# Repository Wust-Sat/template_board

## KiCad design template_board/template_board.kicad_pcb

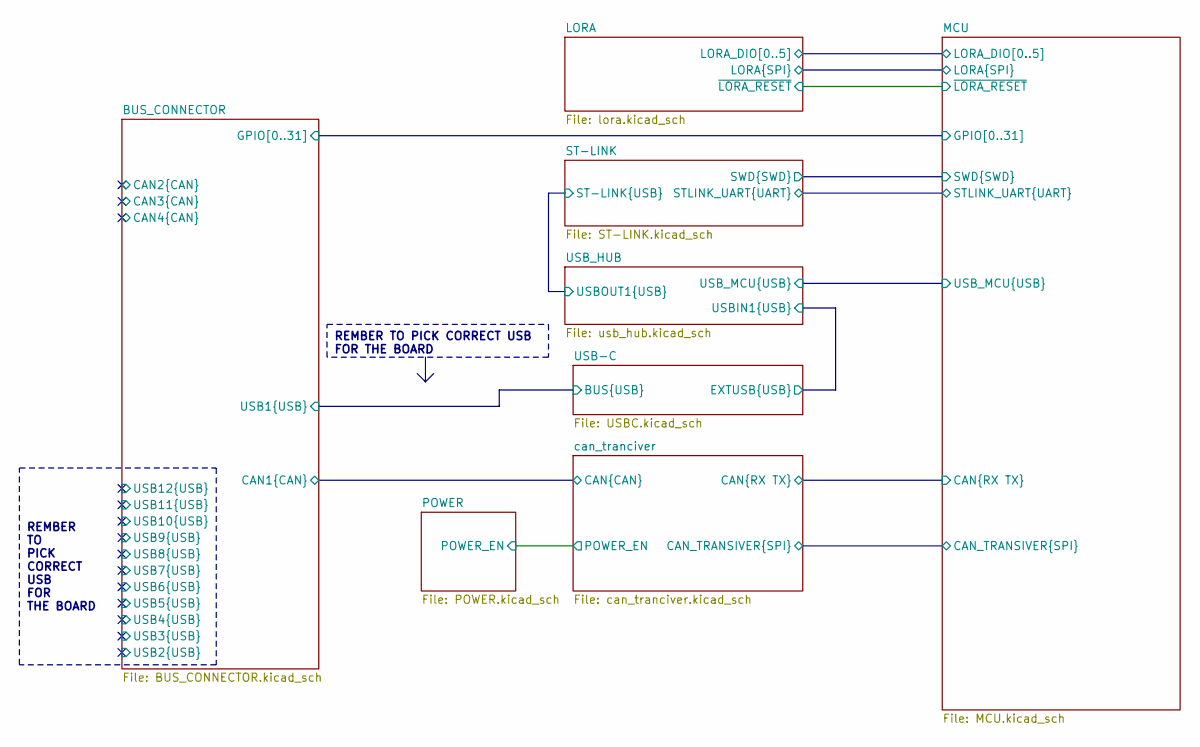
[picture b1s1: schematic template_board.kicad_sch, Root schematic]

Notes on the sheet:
REMBER TO PICK CORRECT USB FOR THE BOARD
REMBER TO PICK CORRECT USB FOR THE BOARD

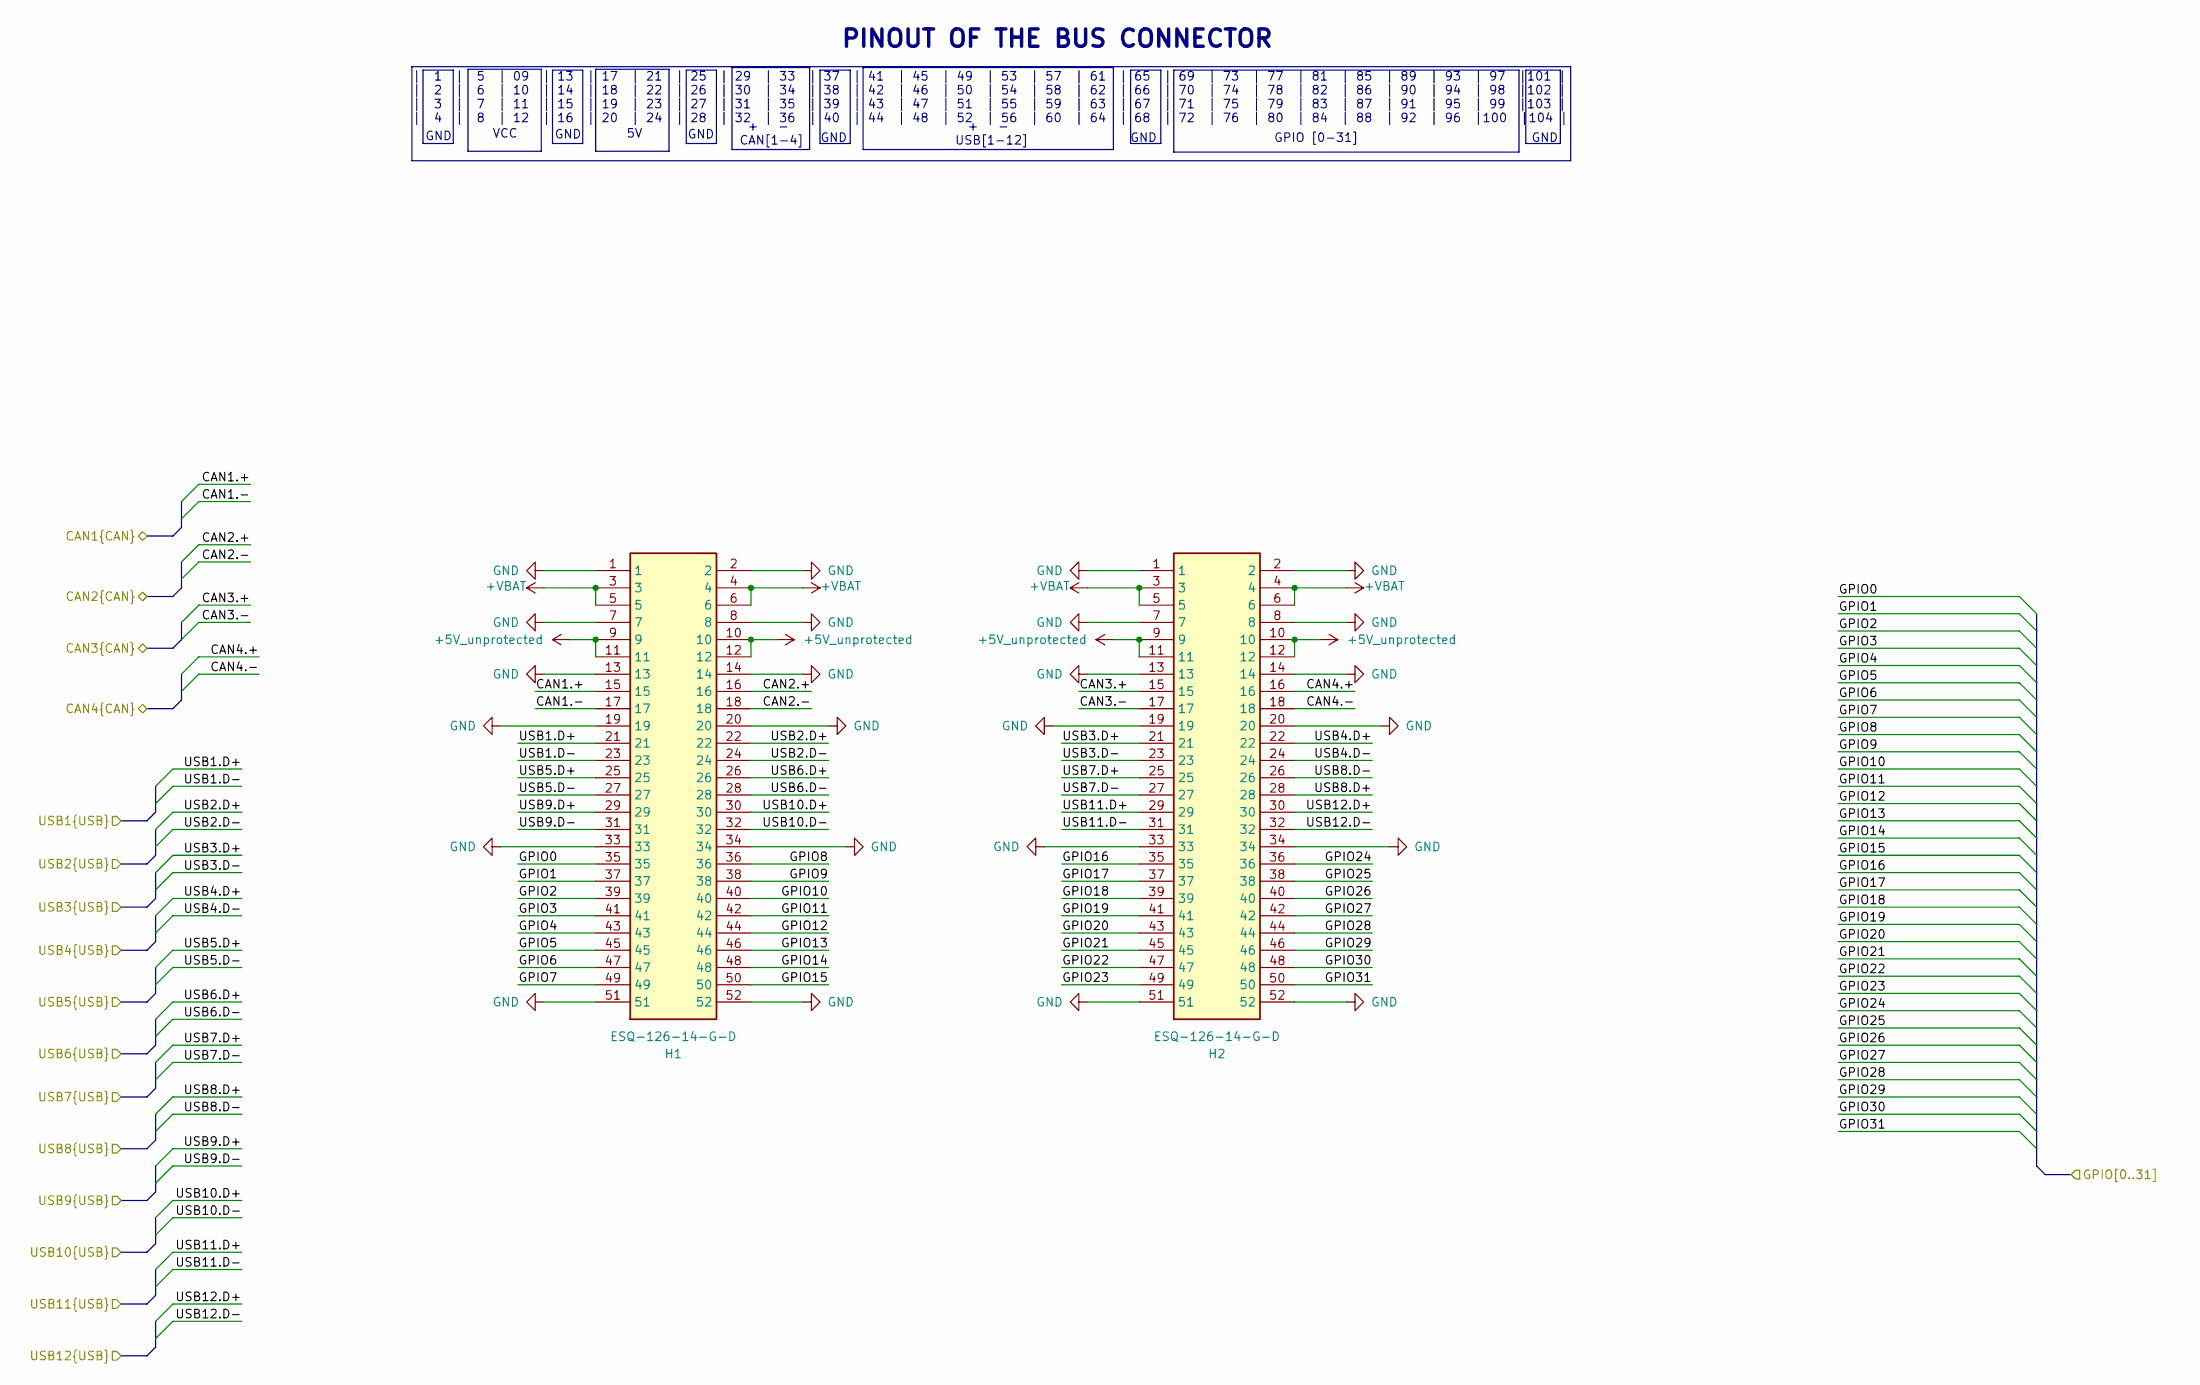
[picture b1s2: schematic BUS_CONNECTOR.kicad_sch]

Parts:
H1, H2: ESQ-126-14-G-D; ESQ-126-Y-X-D; Manufacturer_Part_Number ESQ-126-14-G-D; Mouser Part Number 200-ESQ12614GD

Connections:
+5V_unprotected: H1.9, H1.10, H1.11, H1.12, H2.9, H2.10, H2.11, H2.12; also elsewhere on the board
+VBAT: H1.3, H1.4, H1.5, H1.6, H2.3, H2.4, H2.5, H2.6
/BUS_CONNECTOR/CAN1.+: H1.15; also elsewhere on the board
/BUS_CONNECTOR/CAN1.-: H1.17; also elsewhere on the board
/BUS_CONNECTOR/CAN2.+: H1.16
/BUS_CONNECTOR/CAN2.-: H1.18
/BUS_CONNECTOR/CAN3.+: H2.15
/BUS_CONNECTOR/CAN3.-: H2.17
/BUS_CONNECTOR/CAN4.+: H2.16
/BUS_CONNECTOR/CAN4.-: H2.18
/BUS_CONNECTOR/GPIO0: H1.35; also elsewhere on the board
/BUS_CONNECTOR/GPIO1: H1.37; also elsewhere on the board
/BUS_CONNECTOR/GPIO2: H1.39; also elsewhere on the board
/BUS_CONNECTOR/GPIO3: H1.41; also elsewhere on the board
/BUS_CONNECTOR/GPIO4: H1.43; also elsewhere on the board
/BUS_CONNECTOR/GPIO5: H1.45
/BUS_CONNECTOR/GPIO6: H1.47
/BUS_CONNECTOR/GPIO7: H1.49
/BUS_CONNECTOR/GPIO8: H1.36; also elsewhere on the board
/BUS_CONNECTOR/GPIO9: H1.38; also elsewhere on the board
/BUS_CONNECTOR/GPIO10: H1.40; also elsewhere on the board
/BUS_CONNECTOR/GPIO11: H1.42; also elsewhere on the board
/BUS_CONNECTOR/GPIO12: H1.44; also elsewhere on the board
/BUS_CONNECTOR/GPIO13: H1.46
/BUS_CONNECTOR/GPIO14: H1.48
/BUS_CONNECTOR/GPIO15: H1.50
/BUS_CONNECTOR/GPIO16: H2.35; also elsewhere on the board
/BUS_CONNECTOR/GPIO17: H2.37; also elsewhere on the board
/BUS_CONNECTOR/GPIO18: H2.39; also elsewhere on the board
/BUS_CONNECTOR/GPIO19: H2.41; also elsewhere on the board
/BUS_CONNECTOR/GPIO20: H2.43
/BUS_CONNECTOR/GPIO21: H2.45
/BUS_CONNECTOR/GPIO22: H2.47
/BUS_CONNECTOR/GPIO23: H2.49
/BUS_CONNECTOR/GPIO24: H2.36; also elsewhere on the board
/BUS_CONNECTOR/GPIO25: H2.38; also elsewhere on the board
/BUS_CONNECTOR/GPIO26: H2.40; also elsewhere on the board
/BUS_CONNECTOR/GPIO27: H2.42; also elsewhere on the board
/BUS_CONNECTOR/GPIO28: H2.44
/BUS_CONNECTOR/GPIO29: H2.46
/BUS_CONNECTOR/GPIO30: H2.48
/BUS_CONNECTOR/GPIO31: H2.50
/BUS_CONNECTOR/USB1.D+: H1.21; also elsewhere on the board
/BUS_CONNECTOR/USB1.D-: H1.23; also elsewhere on the board
/BUS_CONNECTOR/USB2.D+: H1.22
/BUS_CONNECTOR/USB2.D-: H1.24
/BUS_CONNECTOR/USB3.D+: H2.21
/BUS_CONNECTOR/USB3.D-: H2.23
/BUS_CONNECTOR/USB4.D+: H2.22
/BUS_CONNECTOR/USB4.D-: H2.24
/BUS_CONNECTOR/USB5.D+: H1.25
/BUS_CONNECTOR/USB5.D-: H1.27
/BUS_CONNECTOR/USB6.D+: H1.26
/BUS_CONNECTOR/USB6.D-: H1.28
/BUS_CONNECTOR/USB7.D+: H2.25
/BUS_CONNECTOR/USB7.D-: H2.27
/BUS_CONNECTOR/USB8.D+: H2.28
/BUS_CONNECTOR/USB8.D-: H2.26
/BUS_CONNECTOR/USB9.D+: H1.29
/BUS_CONNECTOR/USB9.D-: H1.31
/BUS_CONNECTOR/USB10.D+: H1.30
/BUS_CONNECTOR/USB10.D-: H1.32
/BUS_CONNECTOR/USB11.D+: H2.29
/BUS_CONNECTOR/USB11.D-: H2.31
/BUS_CONNECTOR/USB12.D+: H2.30
/BUS_CONNECTOR/USB12.D-: H2.32
GND: H1.1, H1.2, H1.7, H1.8, H1.13, H1.14, H1.19, H1.20, H1.33, H1.34, H1.51, H1.52, H2.1, H2.2, H2.7, H2.8, H2.13, H2.14, H2.19, H2.20, H2.33, H2.34, H2.51, H2.52; also elsewhere on the board

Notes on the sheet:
+ - CAN[1-4]
PINOUT OF THE BUS CONNECTOR
GND
+ - USB[1-12]
VCC
| 1 | 5 | 09 | 13 | 17 | 21 | 25 | 29 | 33 | 37 | 41 | 45 | 49 | 53 | 57 | 61 | 65 | 69 | 73 | 77 | 81 | 85 | 89 | 93 | 97 |101 | | 2 | 6 | 10 | 14 | 18 | 22 | 26 | 30 | 34 | 38 | 42 | 46 | 50 | 54 | 58 | 62 | 66 | 70 | 74 | 78 | 82 | 86 | 90 | 94 | 98 |102 | | 3 | 7 | 11 | 15 | 19 | 23 | 27 | 31 |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
GPIO [0-31]

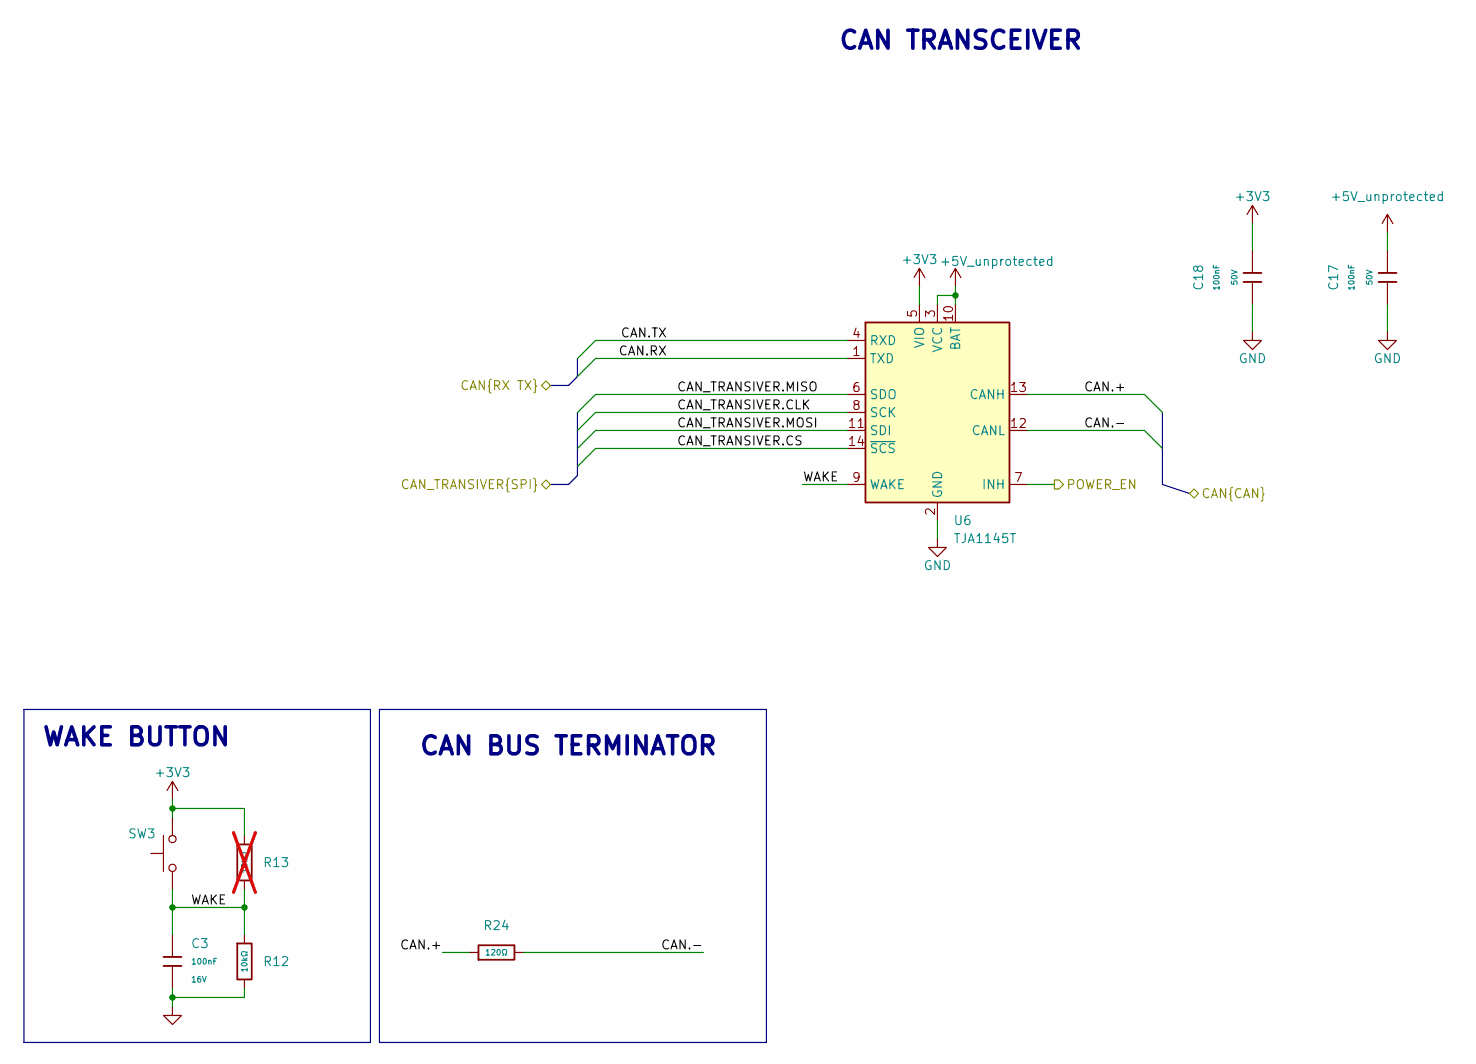
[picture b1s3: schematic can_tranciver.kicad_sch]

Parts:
C3: 100nF; C_0402; Voltage Rated 16V; Tolerance ±10%; Part CL05B104KO5NNNC; LCSC C1525
C17, C18: 100nF; C_0402; Voltage Rated 50V; Tolerance ±10%; Part CL05B104KB54PNC; LCSC C307331
R12: 10kΩ; R_0402; Overload Voltage (Max) 50V; Tolerance ±1%; Part 0402WGF1002TCE; LCSC C25744
R13: 10kΩ; R_0402; Overload Voltage (Max) 50V; Tolerance ±1%; Part 0402WGF1002TCE; LCSC C25744; not fitted
R24: 120Ω; R_0603; Overload Voltage (Max) 75V; Tolerance ±1%; Part 0603WAF1200T5E; LCSC C22787
SW3: SW_Push; TS1088R02026; LCSC C455280
U6: TJA1145T; SOIC-14_3.9x8.7mm_P1.27mm

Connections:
+3V3: C18.2, R13.1, SW3.2, U6.5 (VIO); also elsewhere on the board
+5V_unprotected: C17.2, U6.3 (VCC), U6.10 (BAT); also elsewhere on the board
/BUS_CONNECTOR/CAN1.+: R24.1, U6.13 (CANH); also elsewhere on the board
/BUS_CONNECTOR/CAN1.-: R24.2, U6.12 (CANL); also elsewhere on the board
/MCU/CAN.RX: U6.1 (TXD); also elsewhere on the board
/MCU/CAN.TX: U6.4 (RXD); also elsewhere on the board
/MCU/CAN_TRANSIVER.CLK: U6.8 (SCK); also elsewhere on the board
/MCU/CAN_TRANSIVER.CS: U6.14 (~SCS); also elsewhere on the board
/MCU/CAN_TRANSIVER.MISO: U6.6 (SDO); also elsewhere on the board
/MCU/CAN_TRANSIVER.MOSI: U6.11 (SDI); also elsewhere on the board
/POWER/POWER_EN: U6.7 (INH); also elsewhere on the board
/can_tranciver/WAKE: C3.1, R12.1, R13.2, SW3.1, U6.9 (WAKE)
GND: C3.2, C17.1, C18.1, R12.2, U6.2 (GND); also elsewhere on the board

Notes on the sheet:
CAN TRANSCEIVER
CAN BUS TERMINATOR
WAKE BUTTON

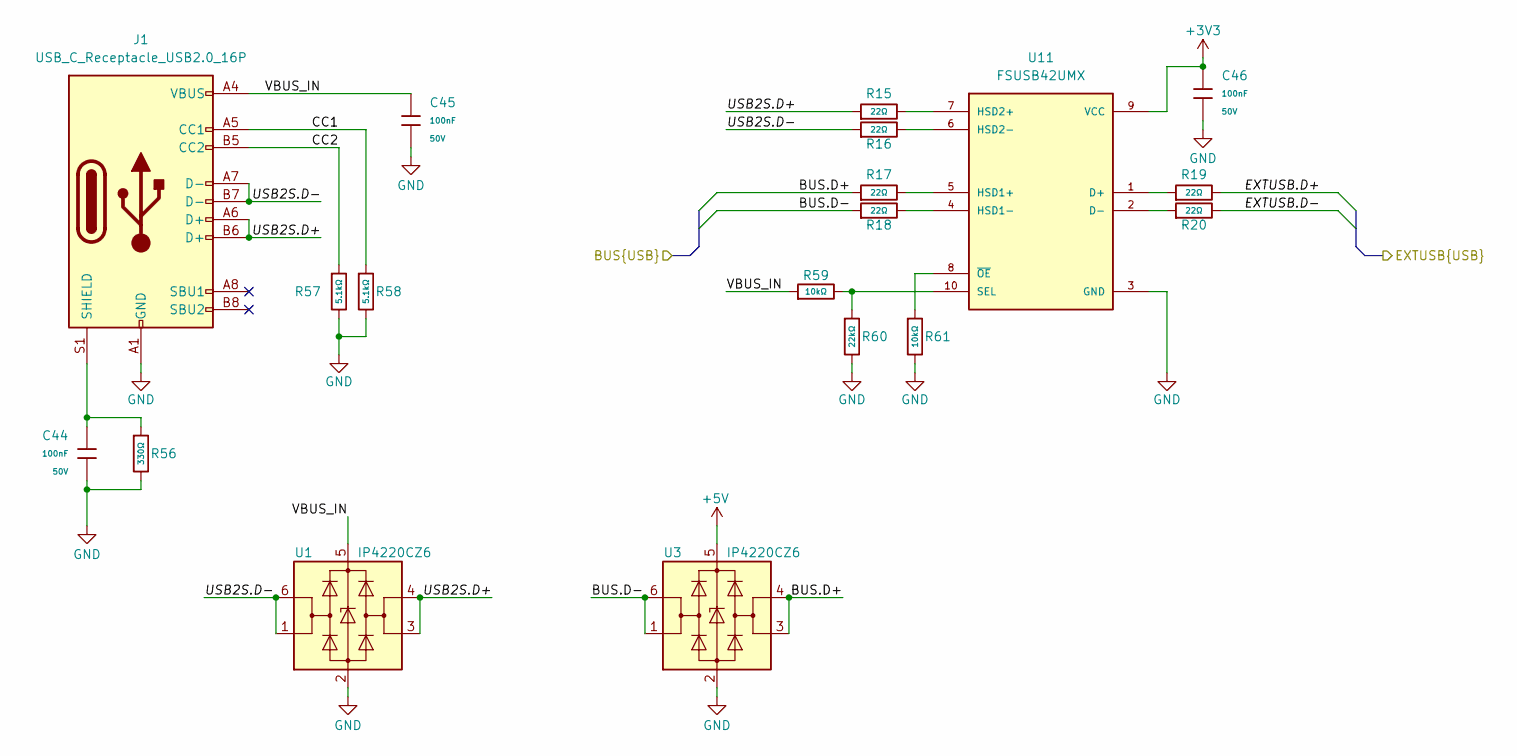
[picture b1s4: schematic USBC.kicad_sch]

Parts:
C44, C45, C46: 100nF; C_0402; Voltage Rated 50V; Tolerance ±10%; Part CL05B104KB54PNC; LCSC C307331
J1: USB_C_Receptacle_USB2.0_16P; USB_C_Receptacle_GCT_USB4105-xx-A_16P_TopMnt_Horizontal
R15, R16, R17, R18, R19, R20: 22Ω; R_0402; Overload Voltage (Max) 50V; Tolerance ±1%; Part 0402WGF220JTCE; LCSC C25092
R56: 330Ω; R_0402; Overload Voltage (Max) 50V; Tolerance ±1%; Part 0402WGF3300TCE; LCSC C25104
R57, R58: 5.1kΩ; R_0402; Overload Voltage (Max) 50V; Tolerance ±1%; Part 0402WGF5101TCE; LCSC C25905
R59, R61: 10kΩ; R_0402; Overload Voltage (Max) 50V; Tolerance ±1%; Part 0402WGF1002TCE; LCSC C25744
R60: 22kΩ; R_0402; Overload Voltage (Max) 50V; Tolerance ±1%; Part 0402WGF2202TCE; LCSC C25768
U1, U3: IP4220CZ6; SOT-23-6
U11: FSUSB42UMX; UQFN-10_1.4x1.8mm_P0.4mm; PARTREV 1.25

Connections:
+3V3: C46.1, U11.9 (VCC); also elsewhere on the board
+5V: U3.5 (VBUS); also elsewhere on the board
/BUS_CONNECTOR/USB1.D+: R17.1, U3.3 (I/O2), U3.4 (I/O2); also elsewhere on the board
/BUS_CONNECTOR/USB1.D-: R18.1, U3.1 (I/O1), U3.6 (I/O1); also elsewhere on the board
/USB-C/CC1: J1.A5 (CC1), R58.1
/USB-C/CC2: J1.B5 (CC2), R57.1
/USB-C/EXTUSB.D+: R19.2; also elsewhere on the board
/USB-C/EXTUSB.D-: R20.2; also elsewhere on the board
/USB-C/USB2S.D+: J1.A6 (D+), J1.B6 (D+), R15.1, U1.3 (I/O2), U1.4 (I/O2)
/USB-C/USB2S.D-: J1.A7 (D-), J1.B7 (D-), R16.1, U1.1 (I/O1), U1.6 (I/O1)
/USB-C/VBUS_IN: C45.1, J1.A4 (VBUS), J1.A9 (VBUS), J1.B4 (VBUS), J1.B9 (VBUS), R59.1, U1.5 (VBUS)
GND: C44.2, C45.2, C46.2, J1.A1 (GND), J1.A12 (GND), J1.B1 (GND), J1.B12 (GND), R56.2, R57.2, R58.2, R60.2, R61.2, U1.2 (GND), U3.2 (GND), U11.3 (GND); also elsewhere on the board
unnamed: C44.1, J1.S1 (SHIELD), R56.1
unnamed: R19.1, U11.1 (D+)
unnamed: R20.1, U11.2 (D-)
unnamed: R17.2, U11.5 (HSD1+)
unnamed: R18.2, U11.4 (HSD1-)
unnamed: R15.2, U11.7 (HSD2+)
unnamed: R16.2, U11.6 (HSD2-)
unnamed: R59.2, R60.1, U11.10 (SEL)
unnamed: R61.1, U11.8 (~OE)

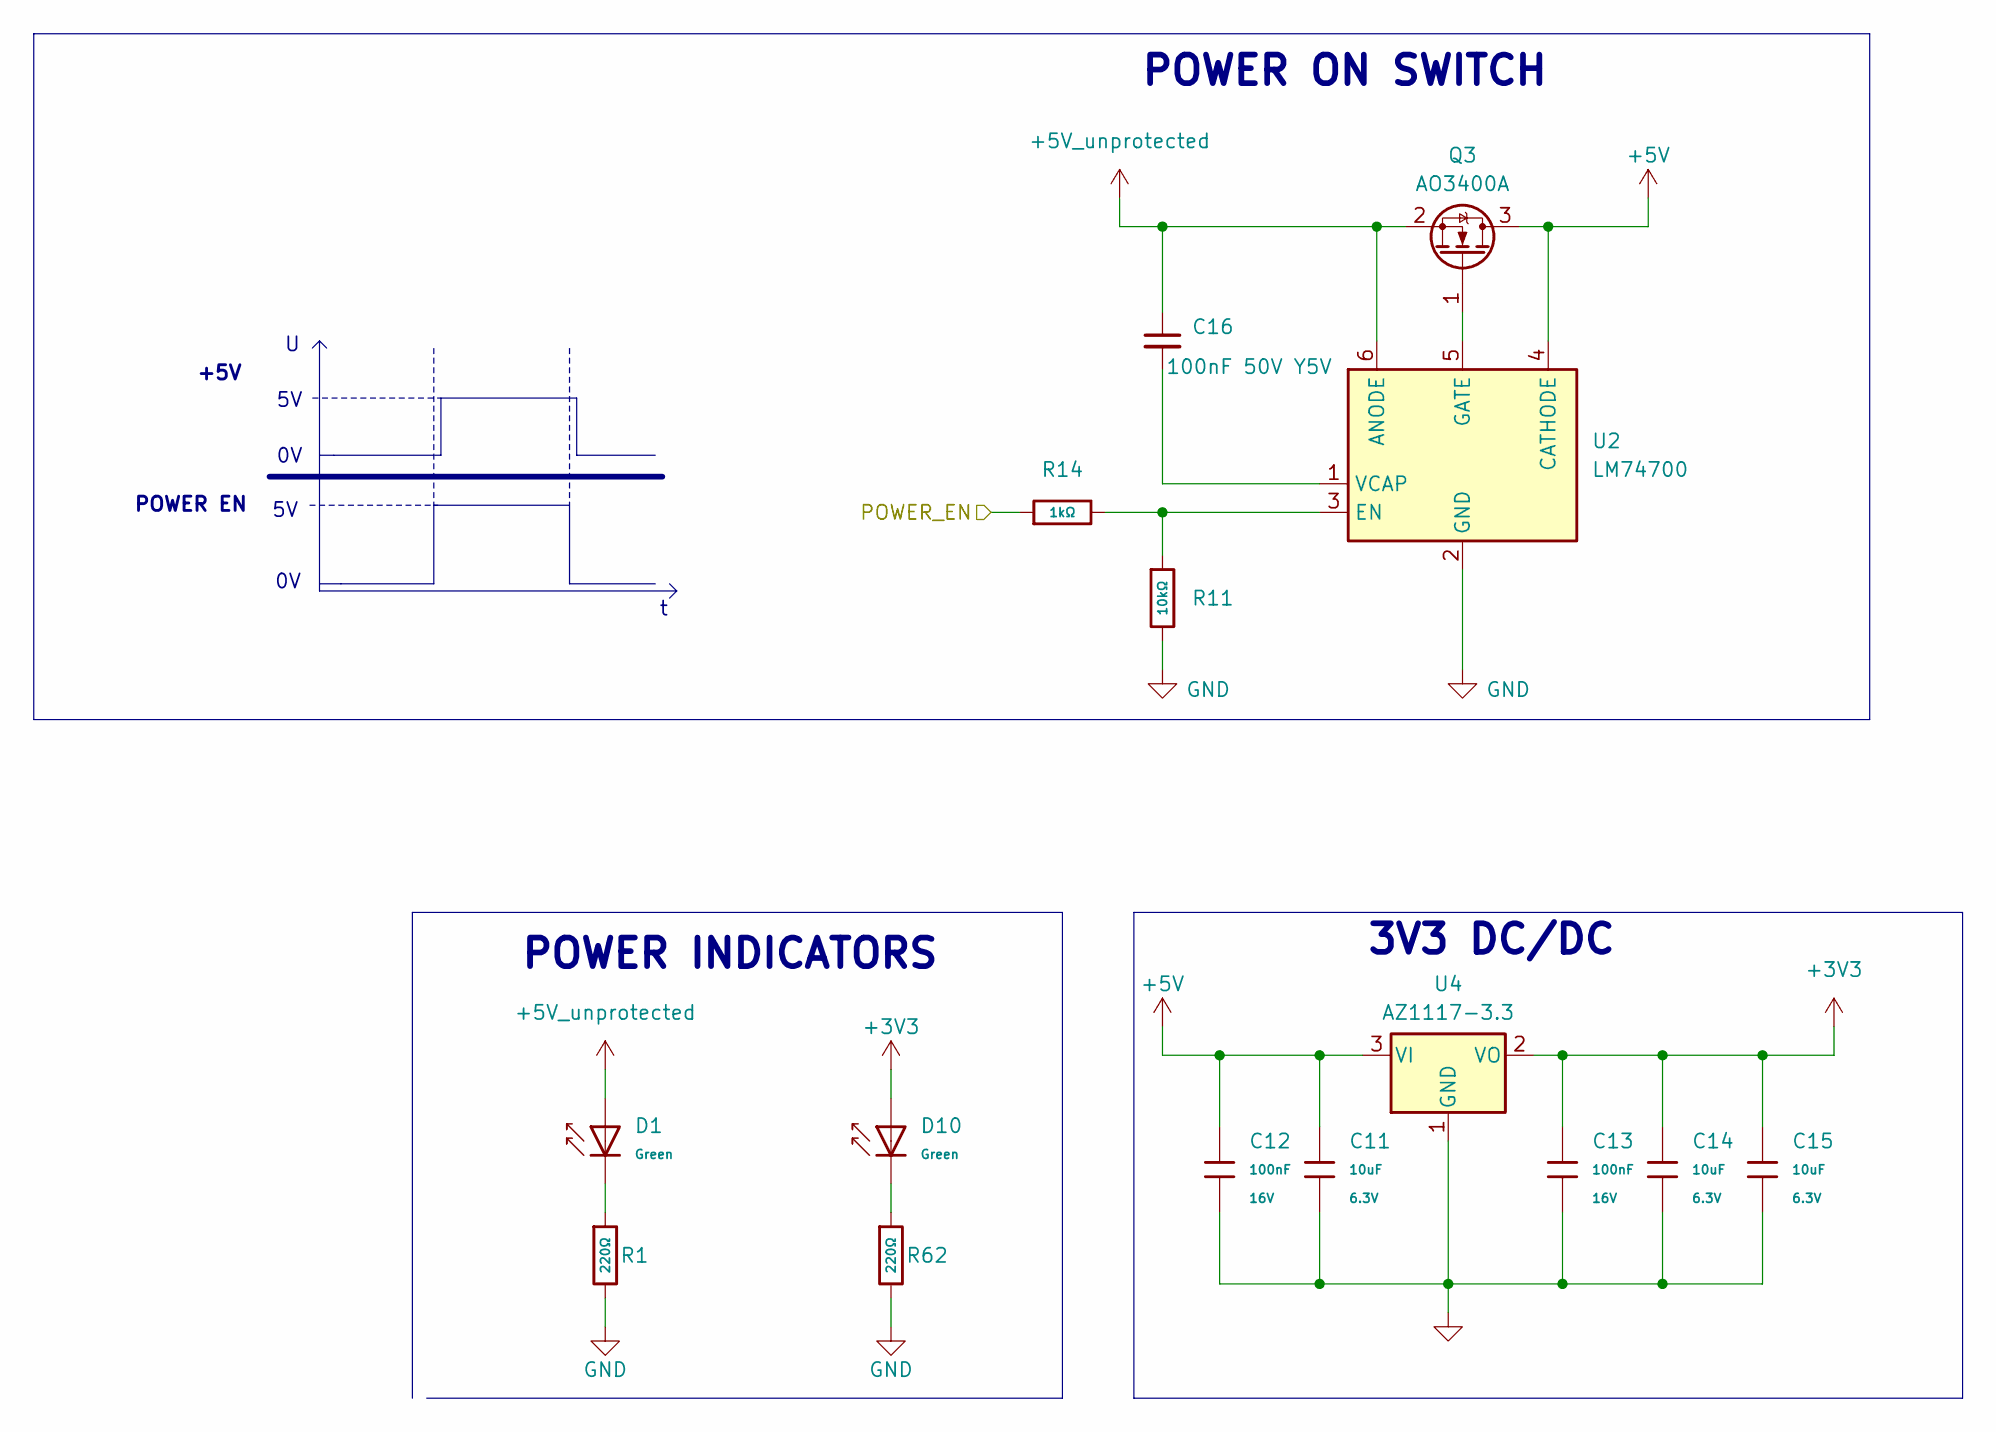
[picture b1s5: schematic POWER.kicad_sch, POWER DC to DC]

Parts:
C11, C14, C15: 10uF; C_0402; Voltage Rated 6.3V; Tolerance ±20%; Part CL05A106MQ5NUNC; LCSC C15525
C12, C13: 100nF; C_0402; Voltage Rated 16V; Tolerance ±10%; Part CL05B104KO5NNNC; LCSC C1525
C16: 100nF 50V Y5V; C_0402_1005Metric
D1, D10: Green; D_0603; Part 19-217/GHC-YR1S2/6T; LCSC C2986059
Q3: AO3400A; SOT-23
R1, R62: 220Ω; R_0402; Overload Voltage (Max) 50V; Tolerance ±1%; Part 0402WGF2200TCE; LCSC C25091
R11: 10kΩ; R_0402; Overload Voltage (Max) 50V; Tolerance ±1%; Part 0402WGF1002TCE; LCSC C25744
R14: 1kΩ; R_0402; Overload Voltage (Max) 50V; Tolerance ±1%; Part 0402WGF1001TCE; LCSC C11702
U2: LM74700; SOT-23-6
U4: AZ1117-3.3; SOT-223-3_TabPin2

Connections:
+3V3: C13.1, C14.1, C15.1, D10.2, U4.2 (VO); also elsewhere on the board
+5V: C11.1, C12.1, Q3.3 (D), U2.4 (CATHODE), U4.3 (VI); also elsewhere on the board
+5V_unprotected: C16.1, D1.2, Q3.2 (S), U2.6 (ANODE); also elsewhere on the board
/POWER/POWER_EN: R14.1; also elsewhere on the board
GND: C11.2, C12.2, C13.2, C14.2, C15.2, R1.2, R11.2, R62.2, U2.2 (GND), U4.1 (GND); also elsewhere on the board
unnamed: D1.1, R1.1
unnamed: D10.1, R62.1
unnamed: Q3.1 (G), U2.5 (GATE)
unnamed: R11.1, R14.2, U2.3 (EN)
unnamed: C16.2, U2.1 (VCAP)

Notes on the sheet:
3V3 DC/DC
POWER EN
+5V
POWER ON SWITCH
POWER INDICATORS

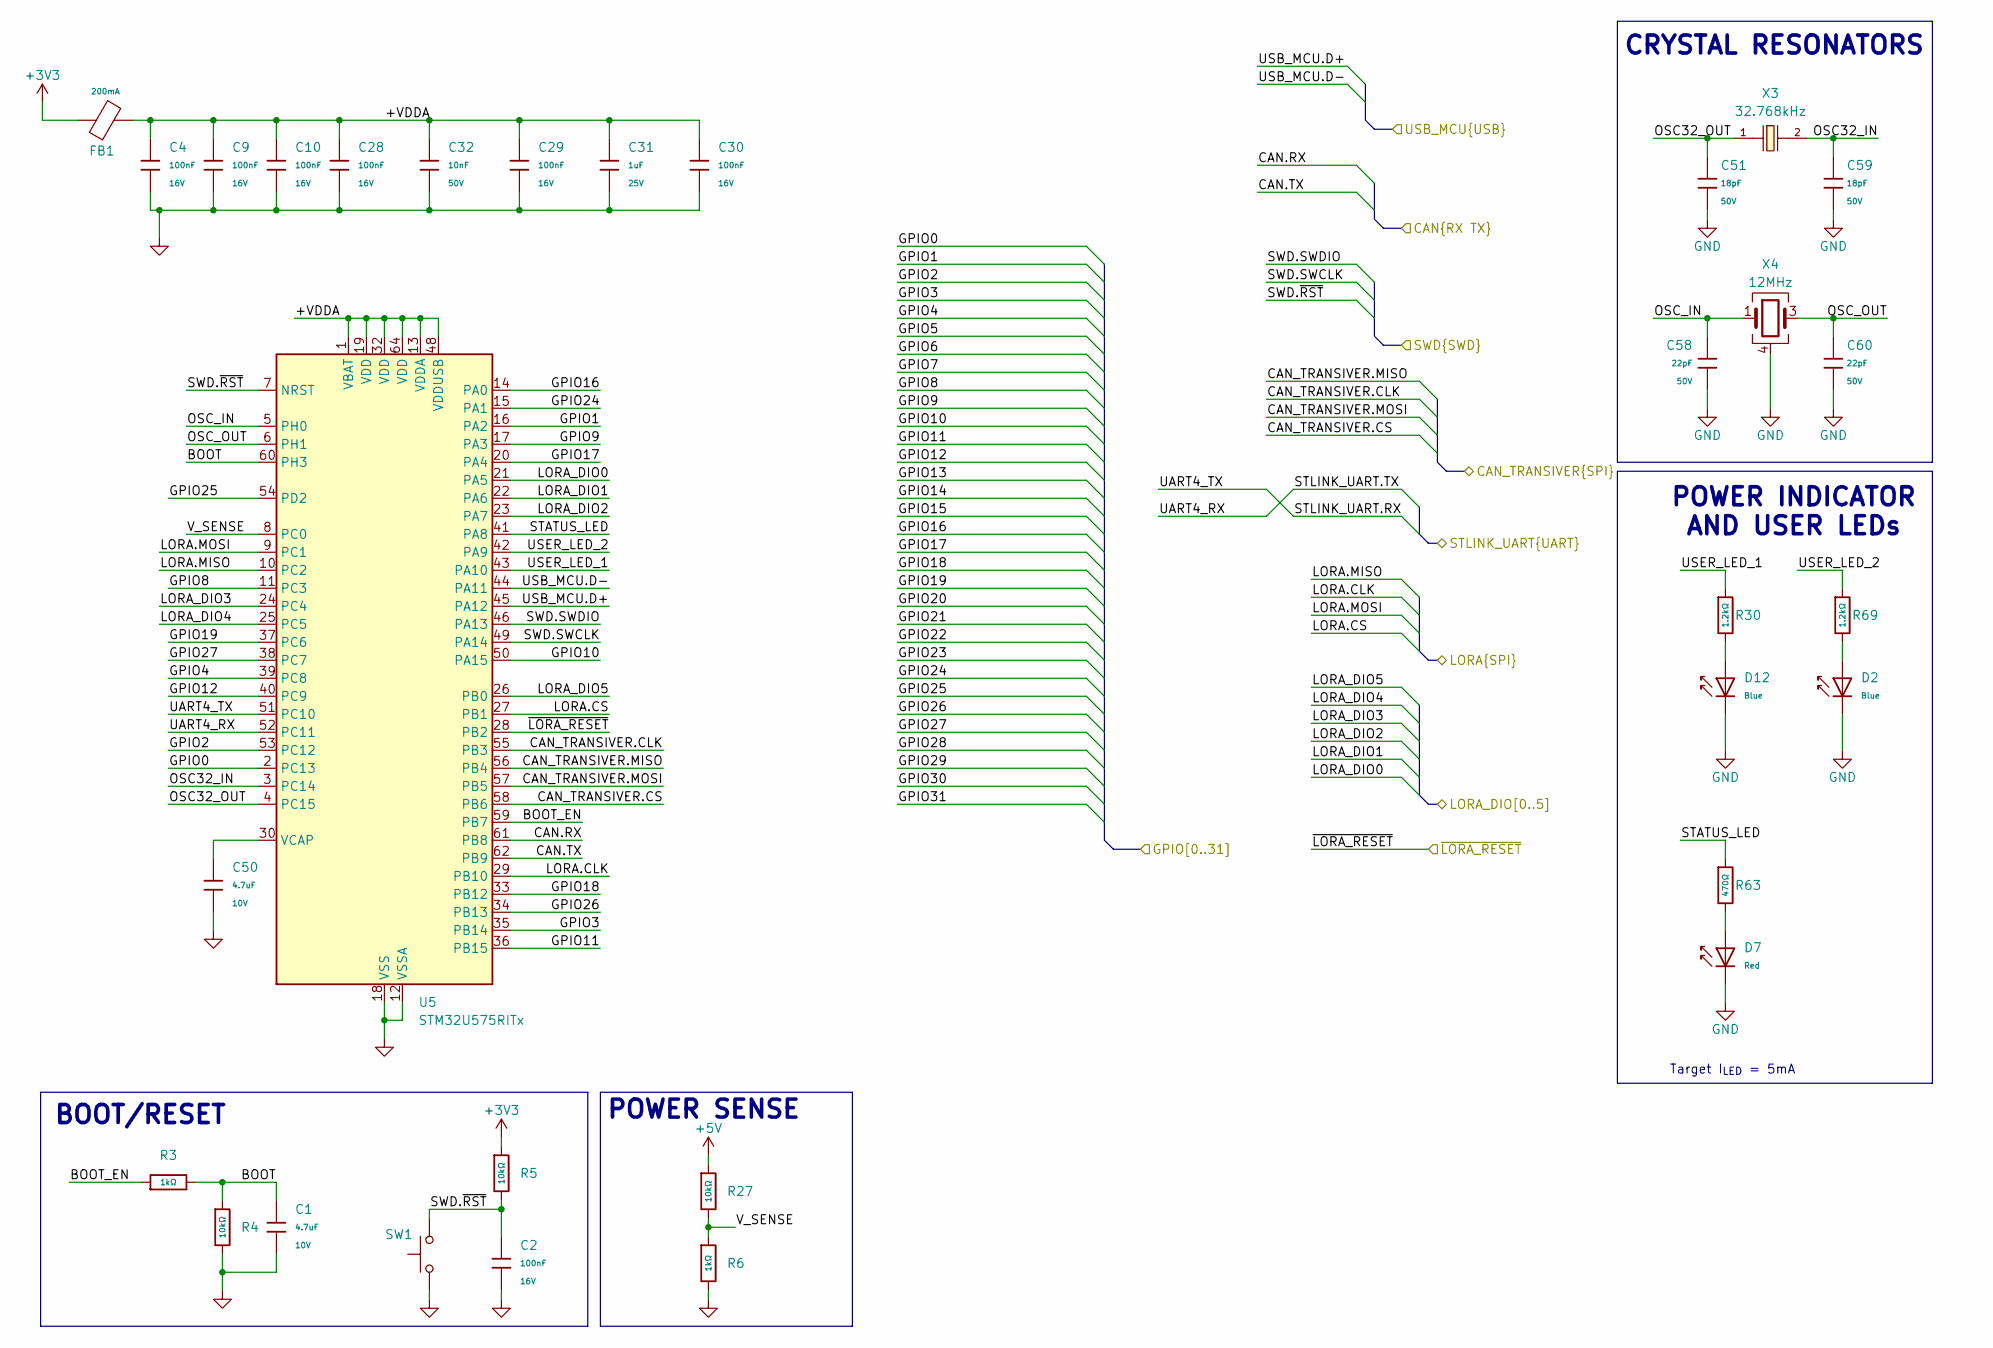
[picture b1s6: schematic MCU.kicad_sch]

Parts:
C1, C50: 4.7uF; C_0402; Voltage Rated 10V; Tolerance ±20%; Part CL05A475MP5NRNC; LCSC C23733
C2, C4, C9, C10, C28, C29, C30: 100nF; C_0402; Voltage Rated 16V; Tolerance ±10%; Part CL05B104KO5NNNC; LCSC C1525
C31: 1uF; C_0402; Voltage Rated 25V; Tolerance ±10%; Part CL05A105KA5NQNC; LCSC C52923
C32: 10nF; C_0402; Voltage Rated 50V; Tolerance ±10%; Part CL05B103KB5NNNC; LCSC C15195
C51, C59: 18pF; C_0402; Voltage Rated 50V; Tolerance ±5%; Part 0402CG180J500NT; LCSC C1549
C58, C60: 22pF; C_0402; Voltage Rated 50V; Tolerance ±5%; Part 0402CG220J500NT; LCSC C1555
D2, D12: Blue; D_0603; Part 19-217/BHC-ZL1M2RY/6T; LCSC C2986058
D7: Red; D_0603; Part KT-0603R; LCSC C2286
FB1: FB_0603; Current Rating 200mA; Tolerance ±25%; Part GZ1608D601TF; LCSC C1002
R3, R6: 1kΩ; R_0402; Overload Voltage (Max) 50V; Tolerance ±1%; Part 0402WGF1001TCE; LCSC C11702
R4, R5, R27: 10kΩ; R_0402; Overload Voltage (Max) 50V; Tolerance ±1%; Part 0402WGF1002TCE; LCSC C25744
R30, R69: 1.2kΩ; R_0402; Overload Voltage (Max) 50V; Tolerance ±1%; Part 0402WGF1201TCE; LCSC C25862
R63: 470Ω; R_0402; Overload Voltage (Max) 50V; Tolerance ±1%; Part 0402WGF4700TCE; LCSC C25117
SW1: SW_Push; TS1088R02026; LCSC C455280
U5: STM32U575RITx; LQFP-64_10x10mm_P0.5mm
X3: Q13FC1350000400; FC-135R_L3.2-W1.5; Frequency Tolerance ±20ppm; Part Q13FC13500004; LCSC C32346
X4: X322512MSB4SI; CRYSTAL-SMD_4P-L3.2-W2.5-BL; Frequency Tolerance ±10ppm; Part X322512MSB4SI; LCSC C9002

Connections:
+3V3: FB1.1, R5.1; also elsewhere on the board
+5V: R27.1; also elsewhere on the board
/BUS_CONNECTOR/GPIO0: U5.2 (PC13); also elsewhere on the board
/BUS_CONNECTOR/GPIO1: U5.16 (PA2); also elsewhere on the board
/BUS_CONNECTOR/GPIO2: U5.53 (PC12); also elsewhere on the board
/BUS_CONNECTOR/GPIO3: U5.35 (PB14); also elsewhere on the board
/BUS_CONNECTOR/GPIO4: U5.39 (PC8); also elsewhere on the board
/BUS_CONNECTOR/GPIO8: U5.11 (PC3); also elsewhere on the board
/BUS_CONNECTOR/GPIO9: U5.17 (PA3); also elsewhere on the board
/BUS_CONNECTOR/GPIO10: U5.50 (PA15); also elsewhere on the board
/BUS_CONNECTOR/GPIO11: U5.36 (PB15); also elsewhere on the board
/BUS_CONNECTOR/GPIO12: U5.40 (PC9); also elsewhere on the board
/BUS_CONNECTOR/GPIO16: U5.14 (PA0); also elsewhere on the board
/BUS_CONNECTOR/GPIO17: U5.20 (PA4); also elsewhere on the board
/BUS_CONNECTOR/GPIO18: U5.33 (PB12); also elsewhere on the board
/BUS_CONNECTOR/GPIO19: U5.37 (PC6); also elsewhere on the board
/BUS_CONNECTOR/GPIO24: U5.15 (PA1); also elsewhere on the board
/BUS_CONNECTOR/GPIO25: U5.54 (PD2); also elsewhere on the board
/BUS_CONNECTOR/GPIO26: U5.34 (PB13); also elsewhere on the board
/BUS_CONNECTOR/GPIO27: U5.38 (PC7); also elsewhere on the board
/LORA/LORA.CLK: U5.29 (PB10); also elsewhere on the board
/LORA/LORA.CS: U5.27 (PB1); also elsewhere on the board
/LORA/LORA.MISO: U5.10 (PC2); also elsewhere on the board
/LORA/LORA.MOSI: U5.9 (PC1); also elsewhere on the board
/LORA/LORA_DIO0: U5.21 (PA5); also elsewhere on the board
/LORA/LORA_DIO1: U5.22 (PA6); also elsewhere on the board
/LORA/LORA_DIO2: U5.23 (PA7); also elsewhere on the board
/LORA/LORA_DIO3: U5.24 (PC4); also elsewhere on the board
/LORA/LORA_DIO4: U5.25 (PC5); also elsewhere on the board
/LORA/LORA_DIO5: U5.26 (PB0); also elsewhere on the board
/LORA/~LORA_RESET: U5.28 (PB2); also elsewhere on the board
/MCU/+VDDA: C4.1, C9.1, C10.1, C28.1, C29.1, C30.1, C31.1, C32.1, FB1.2, U5.1 (VBAT), U5.13 (VDDA), U5.19 (VDD), U5.32 (VDD), U5.48 (VDDUSB), U5.64 (VDD)
/MCU/BOOT: C1.1, R3.2, R4.1, U5.60 (PH3)
/MCU/BOOT_EN: R3.1, U5.59 (PB7)
/MCU/CAN.RX: U5.61 (PB8); also elsewhere on the board
/MCU/CAN.TX: U5.62 (PB9); also elsewhere on the board
/MCU/CAN_TRANSIVER.CLK: U5.55 (PB3); also elsewhere on the board
/MCU/CAN_TRANSIVER.CS: U5.58 (PB6); also elsewhere on the board
/MCU/CAN_TRANSIVER.MISO: U5.56 (PB4); also elsewhere on the board
/MCU/CAN_TRANSIVER.MOSI: U5.57 (PB5); also elsewhere on the board
/MCU/OSC32_IN: C59.1, U5.3 (PC14), X3.2
/MCU/OSC32_OUT: C51.1, U5.4 (PC15), X3.1
/MCU/OSC_IN: C58.1, U5.5 (PH0), X4.1
/MCU/OSC_OUT: C60.1, U5.6 (PH1), X4.3
/MCU/STATUS_LED: R63.1, U5.41 (PA8)
/MCU/STLINK_UART.RX: U5.51 (PC10); also elsewhere on the board
/MCU/STLINK_UART.TX: U5.52 (PC11); also elsewhere on the board
/MCU/SWD.SWCLK: U5.49 (PA14); also elsewhere on the board
/MCU/SWD.SWDIO: U5.46 (PA13); also elsewhere on the board
/MCU/SWD.~RST: C2.1, R5.2, SW1.2, U5.7 (NRST); also elsewhere on the board
/MCU/USB_MCU.D+: U5.45 (PA12); also elsewhere on the board
/MCU/USB_MCU.D-: U5.44 (PA11); also elsewhere on the board
/MCU/USER_LED_1: R30.1, U5.43 (PA10)
/MCU/USER_LED_2: R69.1, U5.42 (PA9)
/MCU/V_SENSE: R6.1, R27.2, U5.8 (PC0)
GND: C1.2, C2.2, C4.2, C9.2, C10.2, C28.2, C29.2, C30.2, C31.2, C32.2, C50.2, C51.2, C58.2, C59.2, C60.2, D2.1, D7.1, D12.1, R4.2, R6.2, SW1.1, U5.12 (VSSA), U5.18 (VSS), U5.31 (VSS), U5.47 (VSS), U5.63 (VSS), X4.2, X4.4; also elsewhere on the board
unnamed: D2.2, R69.2
unnamed: D7.2, R63.2
unnamed: D12.2, R30.2
unnamed: C50.1, U5.30 (VCAP)

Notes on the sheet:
CRYSTAL RESONATORS
POWER SENSE
POWER INDICATOR AND USER LEDs
Target I_{LED} = 5mA
BOOT/RESET

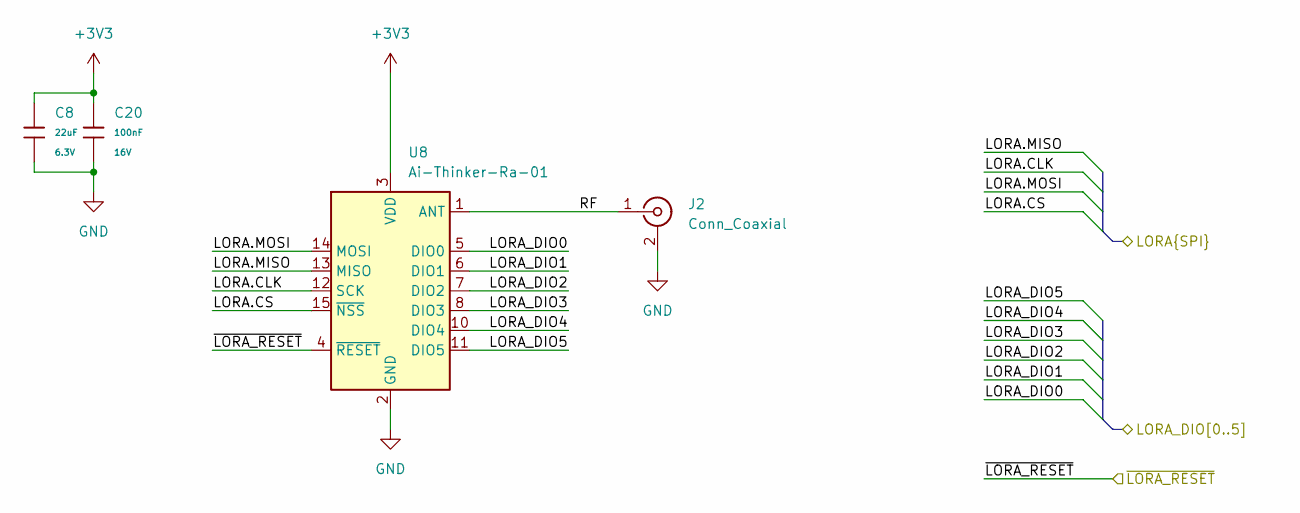
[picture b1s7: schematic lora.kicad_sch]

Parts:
C8: 22uF; C_0603; Voltage Rated 6.3V; Tolerance ±20%; Part CL10A226MQ8NRNC; LCSC C59461
C20: 100nF; C_0402; Voltage Rated 16V; Tolerance ±10%; Part CL05B104KO5NNNC; LCSC C1525
J2: Conn_Coaxial; SMA_Molex_73251-2200_Horizontal
U8: Ai-Thinker-Ra-01; Ai-Thinker-Ra-01-LoRa

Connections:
+3V3: C8.1, C20.1, U8.3 (VDD); also elsewhere on the board
/LORA/LORA.CLK: U8.12 (SCK); also elsewhere on the board
/LORA/LORA.CS: U8.15 (~NSS); also elsewhere on the board
/LORA/LORA.MISO: U8.13 (MISO); also elsewhere on the board
/LORA/LORA.MOSI: U8.14 (MOSI); also elsewhere on the board
/LORA/LORA_DIO0: U8.5 (DIO0); also elsewhere on the board
/LORA/LORA_DIO1: U8.6 (DIO1); also elsewhere on the board
/LORA/LORA_DIO2: U8.7 (DIO2); also elsewhere on the board
/LORA/LORA_DIO3: U8.8 (DIO3); also elsewhere on the board
/LORA/LORA_DIO4: U8.10 (DIO4); also elsewhere on the board
/LORA/LORA_DIO5: U8.11 (DIO5); also elsewhere on the board
/LORA/RF: J2.1 (In), U8.1 (ANT)
/LORA/~LORA_RESET: U8.4 (~RESET); also elsewhere on the board
GND: C8.2, C20.2, J2.2 (Ext), U8.2 (GND), U8.9 (GND), U8.16 (GND); also elsewhere on the board
